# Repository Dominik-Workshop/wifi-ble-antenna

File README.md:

# WiFi BLE Antenna

## Antenna Design

Dimensioning of the antenna simulated in [antenna-design.mat](antenna-design.mat):

### Geometry Parameters
The following parameters (in mm) define the physical layout and PCB dimensions:

| Parameter | Value | Expression / Derived Value |
| :--- | :--- | :--- |
| **D1** | 9 | - |
| **D2** | 2 | - |
| **D3** | 9 | - |
| **D4** | 5 | - |
| **D5** | 17 | - |
| **D6** | 0.5 | - |
| **D7** | 34.5 | - |
| **W1** | 0.8 | - |
| **W2** | 0.5 | - |
| **W3** | 1 | - |
| **L1** | 5.5 | - |
| **L2** | 5.5 | - |
| **L3** | 23.3 | `W1 + D4 + W2 + D5` |
| **PCBwidth** | 42.5 | `D7 + L1 - D6 + W3 + D2` |
| **PCBlength** | 41.3 | `D1 + L3 + D3` |
| **CopperToEdge** | 0.5 | - |

## Simulation Results

### Mesh Settings

To ensure accurate simulation of the resonance and impedance, the following manual meshing parameters were used:

* **Max Edge Length:** `0.025 m` (25 mm)
* **Min Edge Length:** `0.004 m` (4 mm)
* **Growth Rate:** `0.4`

### Return Loss (S11) & Impedance (Z)

Simulated **2.3 - 2.7 GHz** range (`linspace(2.3, 2.7, 80)`):

### Current Distribution

Surface current distribution along the antenna traces at the target resonance:

### Radiation Pattern
2D Azimuth (AZ) and Elevation (EL) far-field radiation patterns:

## Project Status

**Design:** ✅ --> **Fabrication & Assembly:** ✅ --> **Bring-up & Tuning:** ⌛

The project has been assembled and tested. It works, but still needs tuning to meet the target impedance and desired frequency range.
(Note: manufacturing tolerances play a big role in antenna performance.)

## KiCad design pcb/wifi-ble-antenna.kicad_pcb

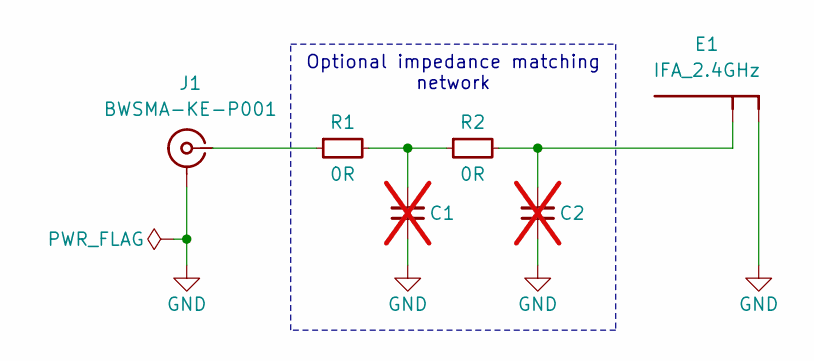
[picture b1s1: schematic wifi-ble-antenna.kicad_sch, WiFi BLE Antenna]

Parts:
C1, C2: C-0402-template; C_0402_1005Metric; Tolerance Tolerance; Voltage Voltage; MPN MPN; LCSC #LCSC; not fitted
E1: IFA_2.4GHz; Antenna_Custom_IFA_2.4GHz
J1: BWSMA-KE-P001; Conn_SMA_BWSMA-KE-P001; MPN BWSMA-KE-P001; LCSC C496550
R1, R2: R-0R-0402; R_0402_1005Metric; Tolerance 1%; MPN 0402WGF0000TCE; LCSC C17168

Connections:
GND: C1.1, C2.1, E1.2 (GND), J1.2
unnamed: C1.2, R1.2, R2.1
unnamed: C2.2, E1.1 (SIG), R2.2
unnamed: J1.1, R1.1

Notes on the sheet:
Optional impedance matching network

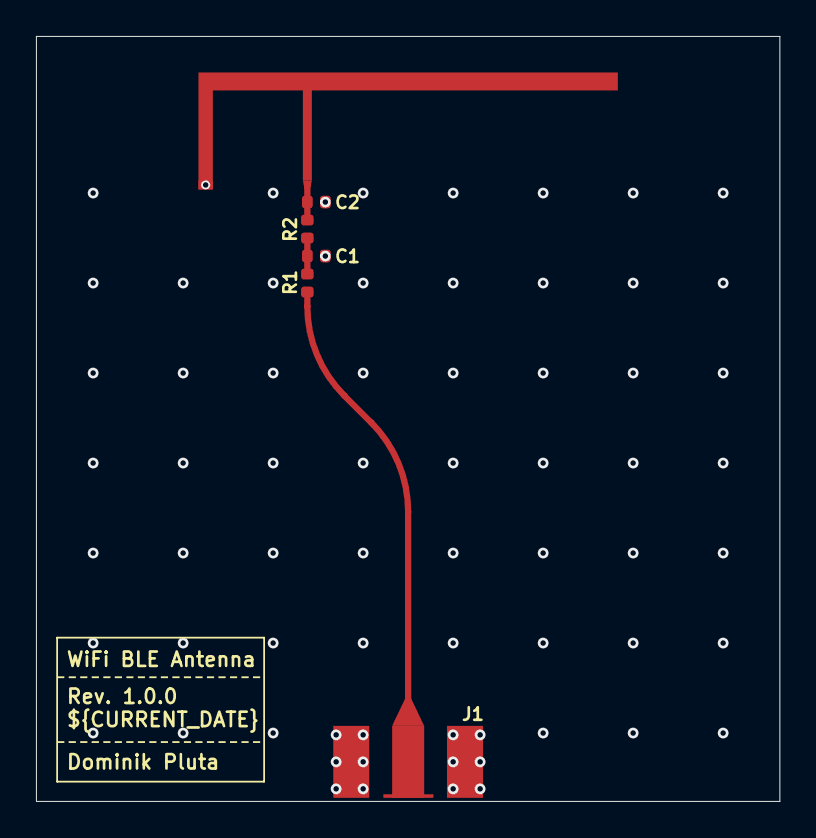
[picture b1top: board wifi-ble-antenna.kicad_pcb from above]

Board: 4 copper layers, 41.3 x 42.5 mm, 6 parts (0 on the bottom side), 4 nets.

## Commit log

2026-03-13 Add LICENSE
2026-03-14 Initialize PCB project
2026-03-14 Sch: Add optional antenna matching network
2026-03-14 Sch: Add SMA connector and antenna, finish schematic
2026-03-27 PCB: Define stackup and pre-defined sizes, init PCB layout
2026-03-27 Add WIP note in README
2026-04-04 Sim: Define PCB dimensions and IFA shape parametricly
2026-04-04 Sim: Merge IFA elements to one polygon
2026-04-04 Add antenna dimensioning diagram in README
2026-04-04 Sim: Add feed point and GND via
2026-04-04 Sim: Define all PCB stackup layers
2026-04-04 Sim: Add GND plane on In1_Cu layer
2026-04-04 Sim: Generate script from the PCB design toolbox
2026-04-04 Sim: Tune the antenna to around 2.46GHz: S11 -34dB, 48Ohm
2026-04-04 Sim: Add GND on In2.Cu, add some stitching vias, tune the IFA initially
2026-04-04 Sim: Remove B.Cu lauer, increase mesh precision, re-tune IFA
2026-04-05 Add simulation parameters and results in README
2026-04-05 PCB: Add IFA, initial layout
2026-04-05 PCB: Finalize layout - add impedance matching geometry to SMA, ensure dimensions are as designed
2026-04-05 PCB: Add stackup table, origin points, cleanup silkscreen, add via stitching
2026-04-05 PCB: Remove solder mask from the antenna
2026-04-05 PCB: Match PCB dimensions exactly with the simulations
2026-04-05 Show CopperToEdge clearance on the antenna dimensioning diagram
2026-04-05 Add PCB render in README, remove WIP note, add project status section
2026-04-05 Update PCB render
2026-04-06 Clear ERC and DRC
2026-04-06 PCB: Move matching network closer to the antenna element
2026-04-06 PCB: Remove soldermask from top and bottom area aroud the antenna
2026-04-06 PCB: Move the PCB info block on silkscreen
2026-04-06 Sim: Update generated script from the PCB Antenna Designer toolbox
2026-04-06 Update project status
